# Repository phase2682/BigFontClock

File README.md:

# BigFontClock
Code for Large Format Number Clock UTC and Local time

Clock display uses all four lines of LCD to display large numbers

Code is written in Python 3.6 for use with Raspbery pi.  Library files are basic code for  
LCD operation and generation of date and time in BCD format

.svg file for enclosure 

checkout https://www.ai6xg.com/post/big-font-clock-relieve-for-old-eyes for more details on software, hardware and build

A PC board for interfacing the LCD to the Rpi W was built in Kicad, schematic and board files now included.  The board has
a 555 based PWM dimmer for a backlit LCD display.  Enclosure has been modified with additional cutout for brightness control.  

See the updated details as https://www.ai6xg.com/post/big-font-clock-update-backlit-lcd     Set up details have also been added.

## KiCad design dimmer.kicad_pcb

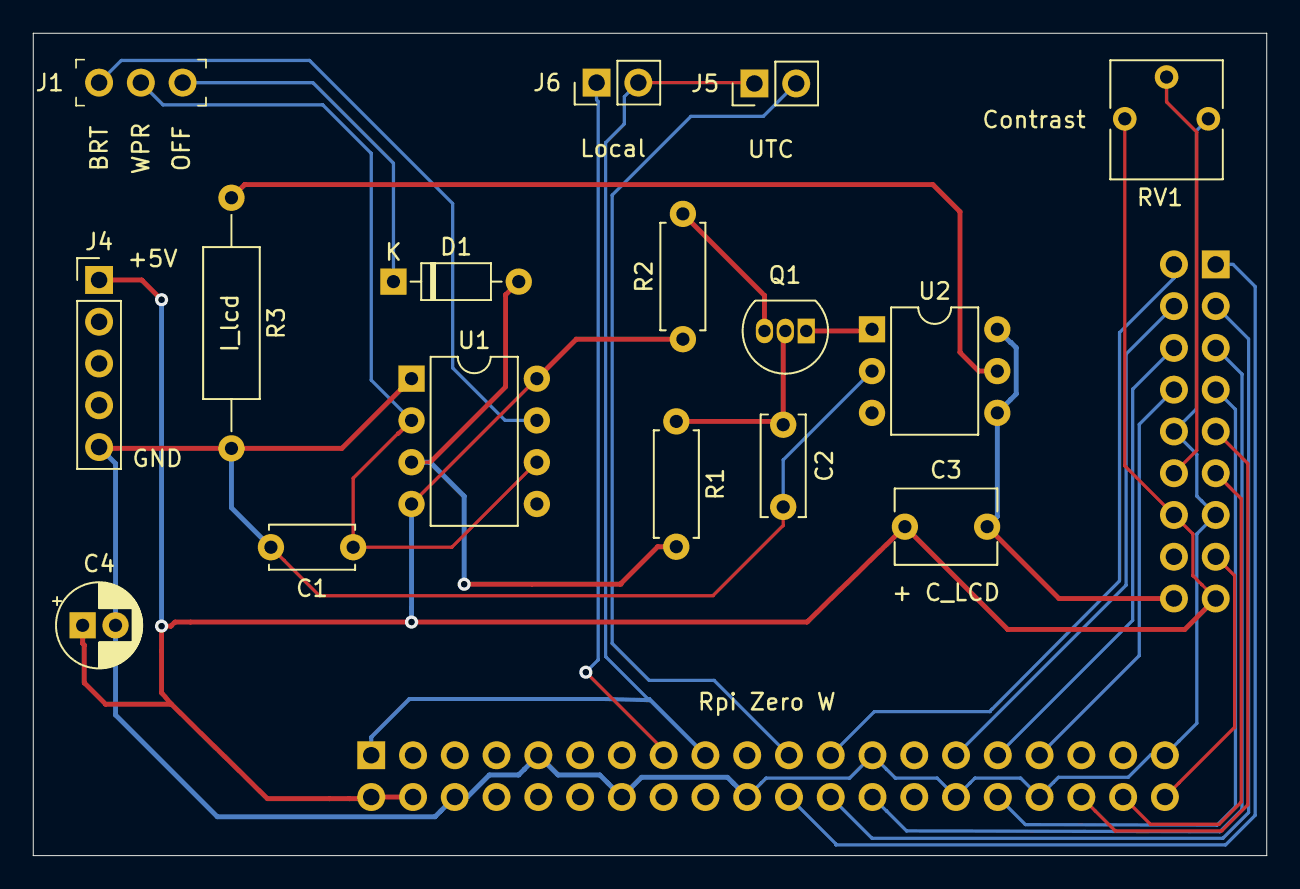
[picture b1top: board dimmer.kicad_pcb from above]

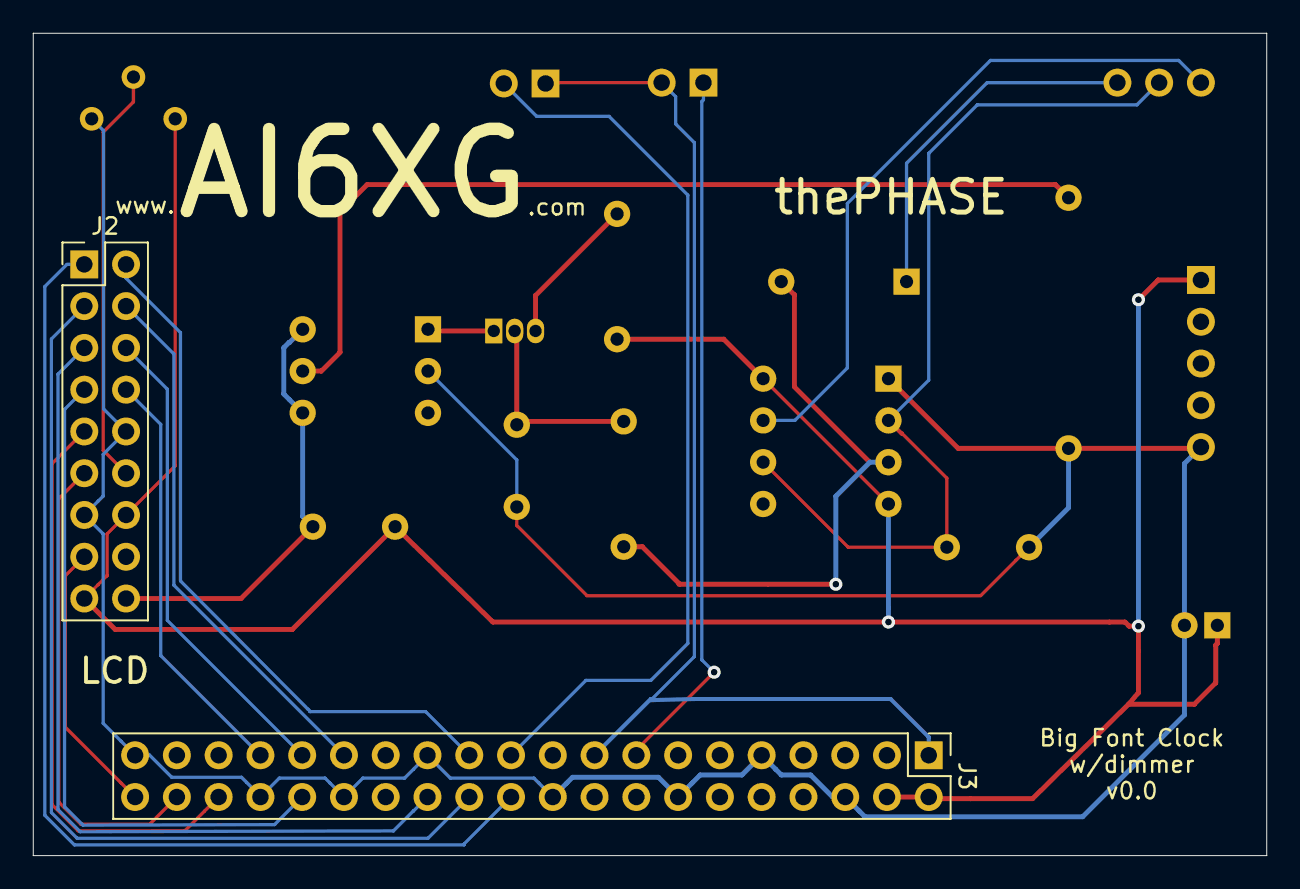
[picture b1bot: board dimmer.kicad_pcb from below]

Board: 2 copper layers, 75.0 x 50.0 mm, 18 parts (2 on the bottom side), 26 nets.

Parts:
C1: 10 nFd; C_Disc_D5.0mm_W2.5mm_P5.00mm
C2: 100n; C_Disc_D6.0mm_W2.5mm_P5.00mm
C3: + C_LCD; C_Disc_D6.0mm_W4.4mm_P5.00mm
C4: 10ufd 16V; CP_Radial_D5.0mm_P2.00mm
D1: BAT43; D_DO-35_SOD27_P7.62mm_Horizontal
J1: 3 pos 2.54mm; PinHeader_1x3_P2.54_Drill1.1mm
J2: LCD; PinHeader_2x09_P2.54mm_Vertical
J3: Raspberry_Pi_Zero_W; PinHeader_2x20_P2.54mm_Vertical
J4: uUSB PWR; PinHeader_1x05_P2.54mm_Vertical
J5: UTC; PinHeader_1x02_P2.54mm_Vertical
J6: Local; PinHeader_1x02_P2.54mm_Vertical
Q1: PN2222A; TO-92_Inline
R1: 810 250mW; R_Axial_DIN0207_L6.3mm_D2.5mm_P7.62mm_Horizontal
R2: 390 250mW; R_Axial_DIN0207_L6.3mm_D2.5mm_P7.62mm_Horizontal
R3: I_lcd; R_Axial_DIN0309_L9.0mm_D3.2mm_P15.24mm_Horizontal
RV1: 10k; Potentiometer_Vishay_T73YP_Vertical
U1: ICM7555; DIP-8_W7.62mm
U2: CPC1510; DIP-6_W7.62mm

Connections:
+3V3: J3.1, J3.17, J5.1, J6.2
+5V: C3.1, C4.1, J2.14, J2.17, J3.2, J3.4, J4.1, R2.1, RV1.3, U1.4, U1.8
DB0: J2.8, J3.33
DB1: J2.7, J3.32
DB2: J2.6, J3.31
DB3: J2.5, J3.26
DB4: J2.4, J3.29
DB5: J2.3, J3.24
DB6: J2.2, J3.23
DB7: J2.1, J3.22
EN0: J2.9, J3.36
EN1: J2.15, J3.40
GND: C1.2, C2.2, C4.2, J2.10, J2.13, J3.6, J3.9, J3.14, J3.20, J3.25, J3.30, J3.34, J3.39, J4.5, R3.2, RV1.1, U1.1, U2.2
LCD_K: C3.2, J2.18, U2.4, U2.6
LSB_M: J3.15, J6.1
unnamed: C1.1, J1.2, U1.2, U1.6
unnamed: C2.1, Q1.2, R1.1
unnamed: D1.1, J1.3
unnamed: D1.2, R1.2, U1.3
unnamed: J1.1, U1.7
unnamed: Q1.1, U2.1
unnamed: Q1.3, R2.2
unnamed: R3.1, U2.5
RS: J2.11, J3.38
USB_M: J3.21, J5.2
VEE: J2.12, RV1.2

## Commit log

2020-02-10 Update README.md
    add details and website information
2020-03-20 Create LICENSE
2020-06-27 add interface and dimmer PC board to project
2020-06-27 Added dimmer interface board files
2020-06-28 enclosure with cutout for back light dimmer pot
